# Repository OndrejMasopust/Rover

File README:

DO NOT USE ANYTHING FROM THIS REPOSITORY AS THIS PROJECT IS NOT FINISHED YET

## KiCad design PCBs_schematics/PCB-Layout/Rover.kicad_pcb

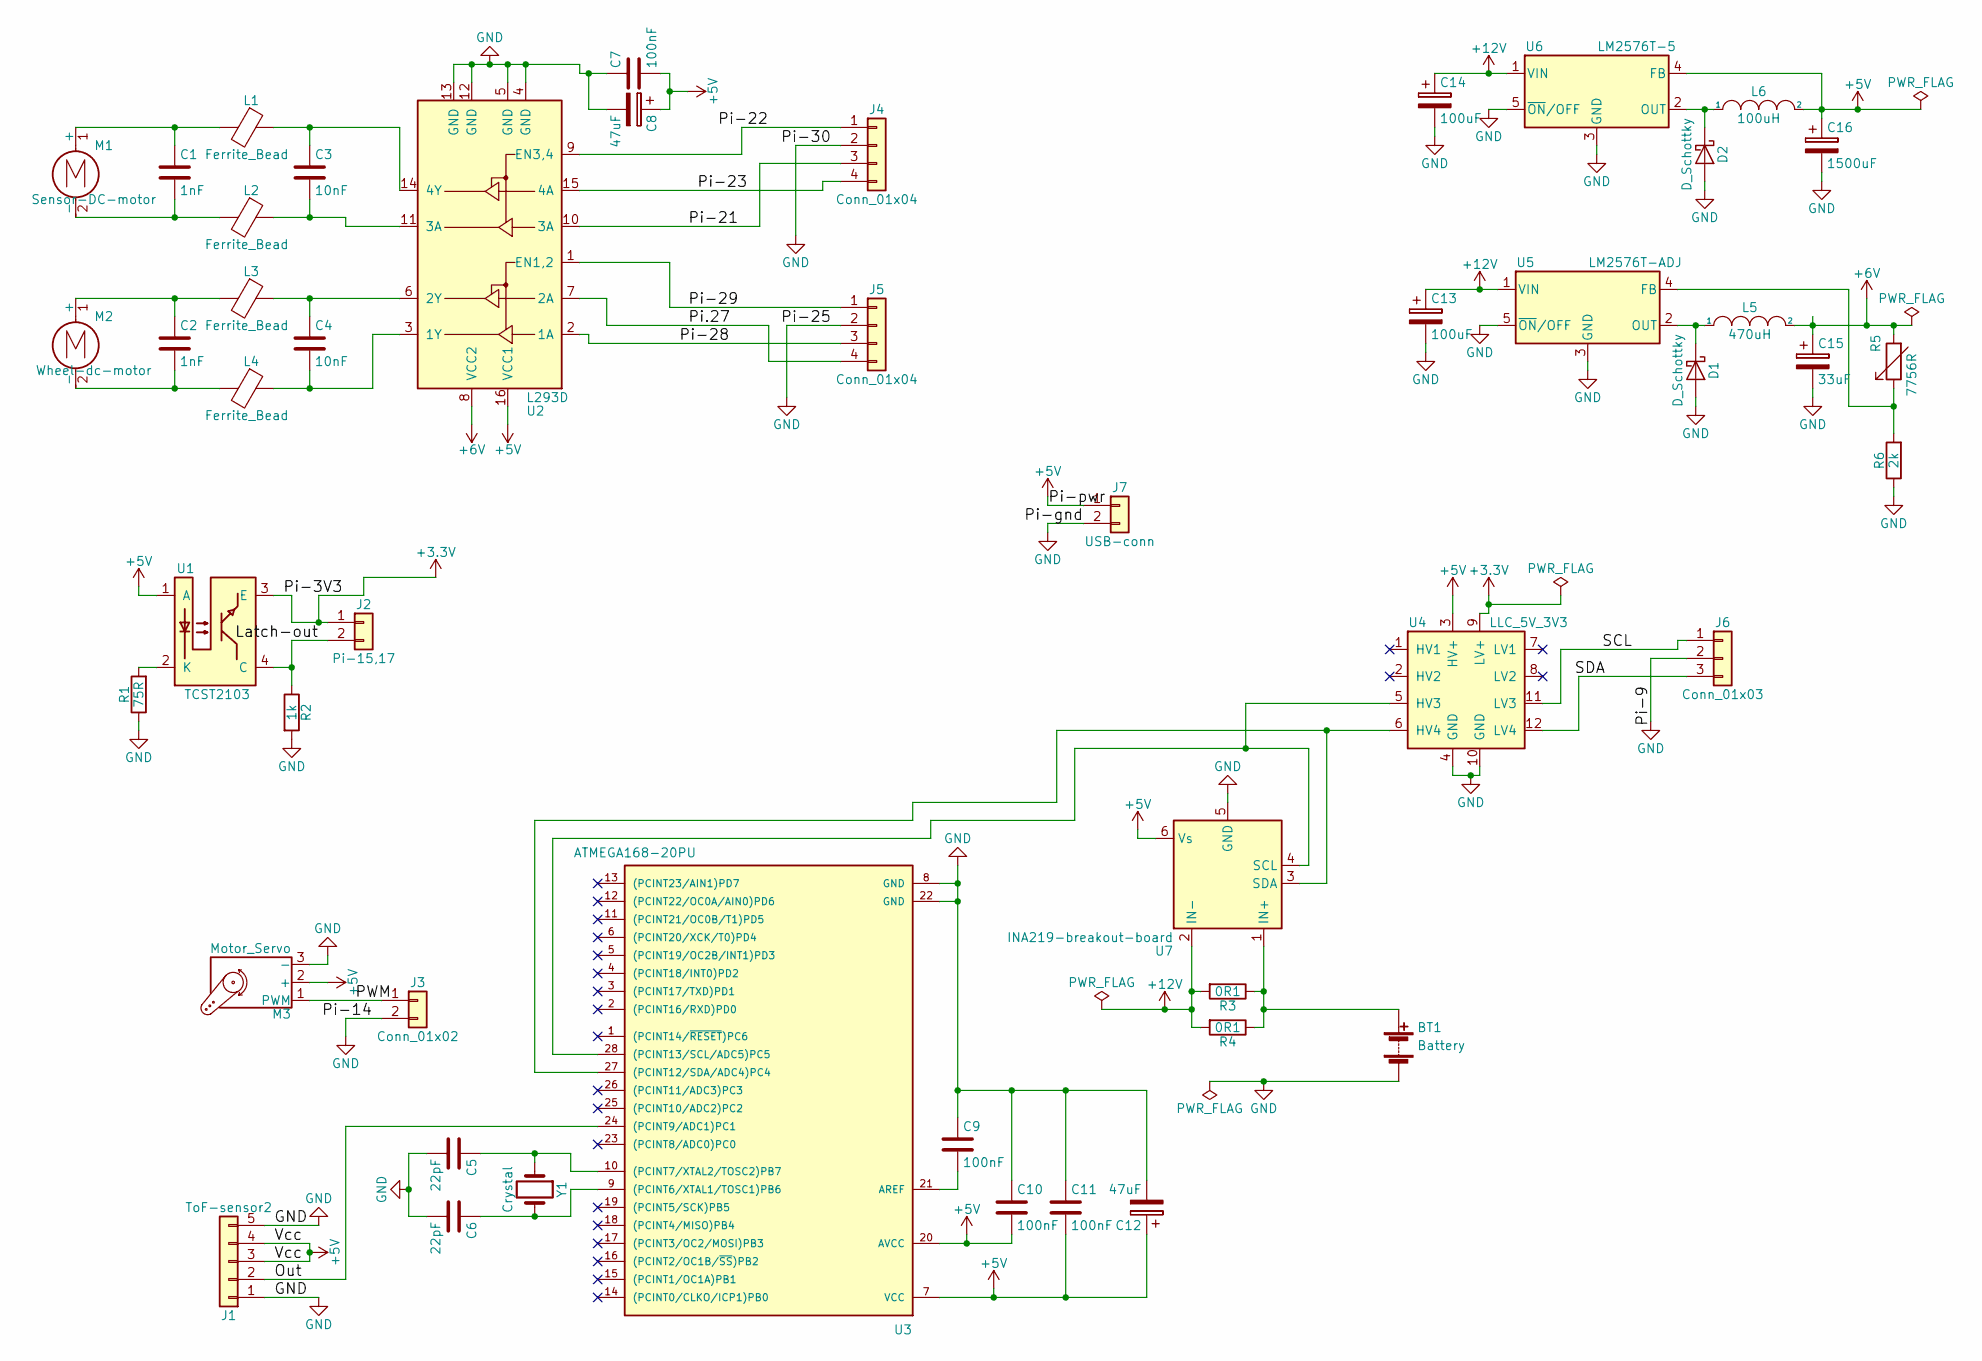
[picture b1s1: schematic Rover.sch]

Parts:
BT1: Battery; WireConnection_0.80mmDrill
C1, C2: 1nF; C_Rect_L7_W2_P5
C3, C4: 10nF; C_Rect_L4_W2.5_P2.5
C5, C6: 22pF; C_Rect_L7_W2_P5
C7, C9, C10, C11: 100nF; C_Rect_L4_W2.5_P2.5
C8, C12: 47uF; C_Rect_L4_W2.5_P2.5
C13: 100uF; C_Rect_L7_W2_P5
C14: 100uF; C_Rect_L4_W2.5_P2.5
C15: 33uF; C_Rect_L4_W2.5_P2.5
C16: 1500uF; C_Rect_L7_W2.5_P5
D1, D2: D_Schottky; Diode_DO-201AD_Horizontal_RM15
J1: ToF-sensor2; Pin_Header_Straight_1x05
J2: Pi-15,17; Pin_Header_Straight_1x02
J3: Conn_01x02; Pin_Header_Straight_1x02
J4, J5: Conn_01x04; Pin_Header_Straight_1x04
J6: Conn_01x03; Pin_Header_Straight_1x03
J7: USB-conn; Pin_Header_Straight_1x02
L1, L2, L3, L4: Ferrite_Bead; WireConnection_2.50mmDrill
L5: 470uH; Resistor_Horizontal_RM7mm
L6: 100uH; Resistor_Horizontal_RM10mm
M1: Sensor-DC-motor; Pin_Header_Straight_1x02
M2: Wheel-dc-motor; Pin_Header_Straight_1x02
M3: Motor_Servo; Pin_Header_Straight_1x03
R1: 75R; Resistor_Horizontal_RM10mm
R2: 1k; Resistor_Horizontal_RM10mm
R3, R4: 0R1; Resistor_Horizontal_RM20mm
R5: 7756R; Potentiometer_Trimmer-Suntan-TSR-3386C
R6: 2k; Resistor_Horizontal_RM10mm
U1: TCST2103; Pin_Header_Straight_1x04
U2: L293D; DIP-16_W7.62mm
U3: ATMEGA168-20PU; DIP-28_W7.62mm
U4: LLC_5V_3V3; LLC-header
U5: LM2576T-ADJ; Pentawatt_Neutral_Straight_Vertical_TO220-5-T05A
U6: LM2576T-5; Pentawatt_Neutral_Straight_Vertical_TO220-5-T05A
U7: INA219-breakout-board; Pin_Header_Straight_1x06
Y1: Crystal; Crystal_HC49-U_Vertical

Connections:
+3V3: J2.1, U1.3 (E), U4.9 (LV+)
+5V: C7.2, C8.1, C10.2, C11.2, C12.1, C16.1, J1.3, J1.4, J7.1, L6.2, M3.2 (+), U1.1 (A), U2.16 (VCC1), U3.7 (VCC), U3.20 (AVCC), U4.3 (HV+), U6.4 (FB), U7.6 (Vs)
+6V: C15.1, L5.2, R5.2, U2.8 (VCC2)
+12V: C13.1, C14.1, R3.2, R4.2, U5.1 (VIN), U6.1 (VIN), U7.2 (IN-)
/Latch-out: J2.2, R2.1, U1.4 (C)
/Out: J1.2, U3.24 ((PCINT9/ADC1)PC1)
/PWM: J3.1, M3.1 (PWM)
/Pi-21: J4.3, U2.10 (3A)
/Pi-22: J4.1, U2.9 (EN3,4)
/Pi-23: J4.4, U2.15 (4A)
/Pi-28: J5.3, U2.2 (1A)
/Pi-29: J5.1, U2.1 (EN1,2)
/Pi.27: J5.4, U2.7 (2A)
/SCL: J6.1, U4.11 (LV3)
/SDA: J6.3, U4.12 (LV4)
GND: BT1.2 (-), C5.2, C6.2, C7.1, C8.2, C9.1, C10.1, C11.1, C12.2, C13.2, C14.2, C15.2, C16.2, D1.2 (A), D2.2 (A), J1.1, J1.5, J3.2, J4.2, J5.2, J6.2, J7.2, M3.3 (-), R1.1, R2.2, R6.1, U2.4 (GND), U2.5 (GND), U2.12 (GND), U2.13 (GND), U3.8 (GND), U3.22 (GND), U4.4 (GND), U4.10 (GND), U5.3 (GND), U5.5 (~ON~/OFF), U6.3 (GND), U6.5 (~ON~/OFF), U7.5 (GND)
unnamed: BT1.1 (+), R3.1, R4.1, U7.1 (IN+)
unnamed: C1.1, L1.2, M1.1 (+)
unnamed: C1.2, L2.2, M1.2 (-)
unnamed: C2.1, L3.2, M2.1 (+)
unnamed: C2.2, L4.2, M2.2 (-)
unnamed: C3.1, L1.1, U2.14 (4Y)
unnamed: C3.2, L2.1, U2.11 (3A)
unnamed: C4.1, L3.1, U2.6 (2Y)
unnamed: C4.2, L4.1, U2.3 (1Y)
unnamed: C5.1, U3.10 ((PCINT7/XTAL2/TOSC2)PB7), Y1.1
unnamed: C6.1, U3.9 ((PCINT6/XTAL1/TOSC1)PB6), Y1.2
unnamed: C9.2, U3.21 (AREF)
unnamed: D1.1 (K), L5.1, U5.2 (OUT)
unnamed: D2.1 (K), L6.1, U6.2 (OUT)
unnamed: R1.2, U1.2 (K)
unnamed: R5.1, R6.2, U5.4 (FB)
unnamed: U3.27 ((PCINT12/SDA/ADC4)PC4), U4.6 (HV4), U7.3 (SDA)
unnamed: U3.28 ((PCINT13/SCL/ADC5)PC5), U4.5 (HV3), U7.4 (SCL)

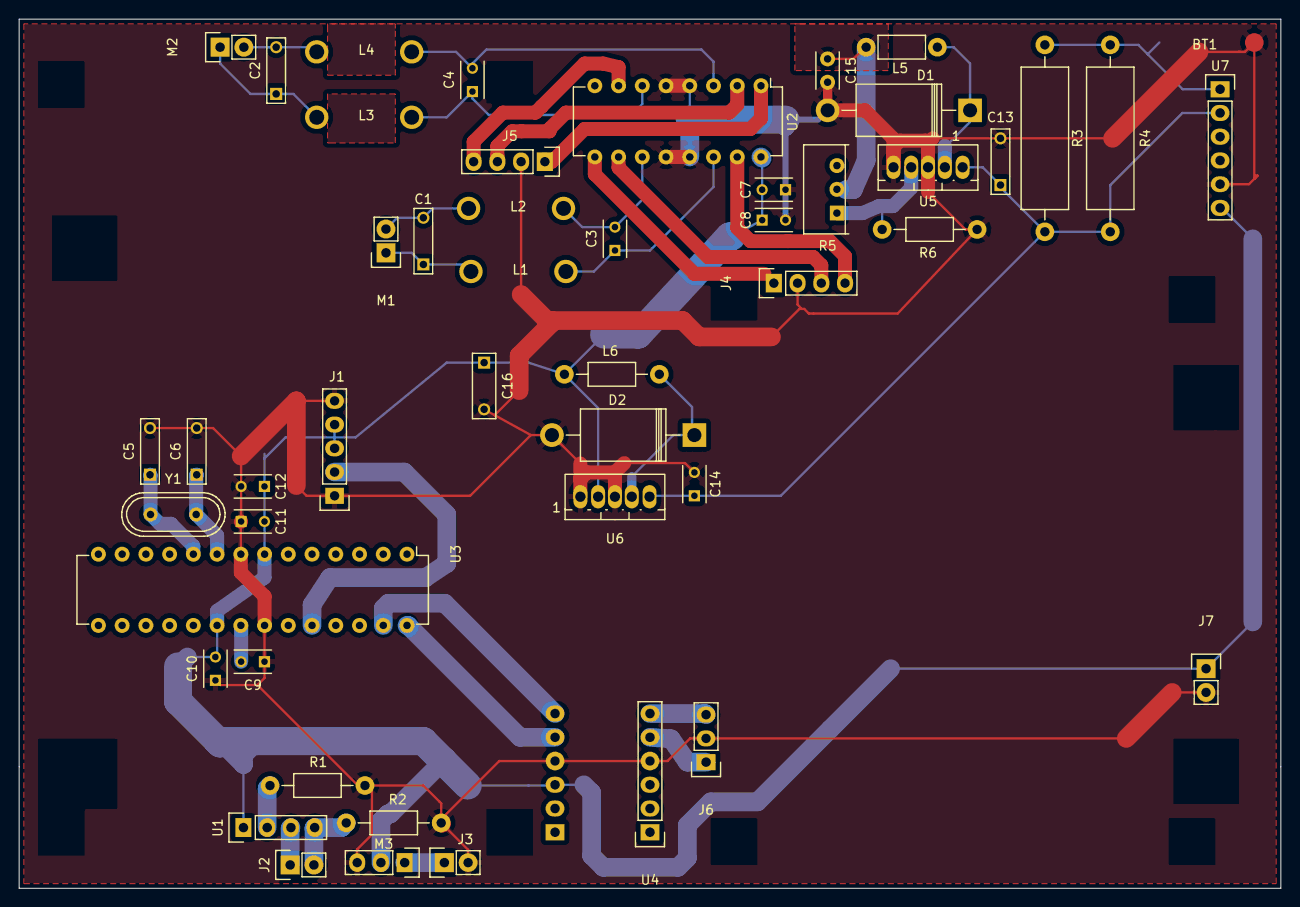
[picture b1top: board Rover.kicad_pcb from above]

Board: 2 copper layers, 135.0 x 93.0 mm, 49 parts (0 on the bottom side), 34 nets.

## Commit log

2017-08-16 Added .gitignore
2017-08-16 fixed bug where I couldn't access Pane from Java code
2017-08-17 compiled files excluded
2017-08-17 organized and added preloader
2017-08-17 preloader works while trying to connect to the Rover
2017-08-17 threads are working properly
2017-08-17 connection thread extends Task<Void>
2017-08-17 minor modifications
2017-08-18 minor changes
2017-08-20 error messages are written to the preloader
2017-08-23 IP selection window works somehow
2017-08-23 preloader in testing conditions, some work done to the rest
2017-08-23 preloader works good with the testing class
2017-08-23 preloader works good with the standard classes
2017-08-24 code cleaning and organizing
2017-08-25 comments added
2017-08-25 some work done
2017-08-26 some more work done on the main layout
2017-08-26 send messages appear on the right in the console
2017-08-28 info works somehow, need to finish it
2017-08-28 little progress
2017-08-29 info ready to edit and some work done on receiving from RPi
2017-08-29 receiving messages from the Rover should work
2017-08-30 adding messages to console works. auto.scroll of the console doesn't work
2017-08-31 console autoscroll in the main layout works
2017-09-01 more work done
2017-09-01 git repo moved one folder down
2017-09-01 some little cleaning
2017-09-01 added server socket testing class that doesn't work properly
2017-09-01 added heading to the console
2017-09-04 progress in the python files
2017-10-09 added event handlers for arrow keys that don't work properly
2017-10-09 now event handlers work unless focus is on the console input TextBox
2017-10-09 arrow key events now work properly but still not finished
2017-10-21 styled the whole app and changed arrow key events to switch-case
2017-10-21 excluded original images
2017-11-13 Lego added and some minor modifications in the software that I don't know what they are.
2017-11-13 progress on lego
2017-11-13 deleted compiled files and edited .gitignore to not track these files
2017-11-29 car design progress
2017-12-31 I2C test were successful
2018-01-03 AVR code is working for 2 sensors
2018-01-20 percentage added to the application and motor and servo drivers tested on RPi
2018-01-23 cleaned some minor errors in the last commit
2018-01-24 anchor commit before doing something crazy
2018-01-27 edited schematics, progress on the Rover software
2018-01-27 added README
2018-02-01 md edit
2018-02-02 commented all necessary in the Python code and renamed PCBs folder to PCBs_schematics
2018-02-02 progress on the python code, cleaned testing python modules into 'test' packages
2018-02-03 Java app now sends 'stop' when closing and waits for the Rover to ACK that
2018-02-03 deleted I2C class from the python code as it ws not used
2018-02-03 Java app can display errors in red, Python sometimes sends them and some more work done
2018-02-03 delted Errors to show in red because it's more difficult than I thought it would be
2018-02-05 Java app receives 'dt' correctly
2018-02-23 added 6V buck-converter version to the schematic
2018-02-23 fixed writing 'bt' commands to the console
2018-02-23 error messages show again in red and every new message has its own box
2018-03-03 progress on the PCB
2018-03-06 more progress on the PCBs
2018-03-07 ferrite beads pads smallered
2018-03-07 edited pcb files for production
2018-03-15 first step of designing mounts of the PCB on the Rover
2018-03-16 some more work done on the Rover Lego design
2018-03-16 final Rover design
2018-03-23 added building instructions for the Rover
2018-03-29 added Credits.md
2018-03-29 edited Credits.md
2018-03-30 fixed defining unused pins on the AVR for lower power consumption
2018-03-30 renamed General-scheme folder
2018-03-30 added the ability to stop the sensor temporarily
2018-03-30 pigpiod server now starts from the Python script
2018-03-31 renamed folder and added value to the crytal
2018-04-02 servo works, main motor changes direction, but the enums for changing directions are not treated as booleans
2018-04-02 added credits for the send arrow icon in the main layout
2018-04-02 edited credits
2018-04-02 added credits to Blackberry for their colot pallete
2018-04-02 added link to the documentation in the README.md
2018-04-02 some testing
2018-04-02 edited comments
2018-04-02 pigpiod server is now stopped when the program is ending
2018-04-02 edited HoeTo.md
2018-04-02 edited Rover lego design
2018-04-02 just save before some experiments
2018-04-02 some code cleaning
2018-04-02 added info to the main layout as html
2018-04-02 save after generating the building instructions
2018-04-02 experiment
2018-04-02 edited HowTo.md
2018-04-02 edited .gitignore
2018-04-02 deleted I2C.rtf from the git repo
2018-04-02 added documentation for the C and edited HowTo
2018-04-04 fixed AVR I2C bug, now it responses to the i2cdetect
2018-04-10 translated HowTo to czech
2018-04-10 edited docs/
2018-04-10 python code works, but queues slow it down, commit before testing Pipe
2018-04-11 exchanged threading.Event instead of queue, between main thread and sensor thread
2018-04-13 commit before testing sending data without the select.select()
2018-04-13 sensing still does not work as expected
2018-04-13 data processing is not fast enough
2018-04-13 deleted pyc files and directories
2018-04-13 ignoring *pyc* files
2018-04-13 Python code shortened, processing data is fast enough
2018-04-13 Java code accepts new type of 'dt' messages, but hangs on quit when the sensor is running
2018-04-14 final changes to the Java program
2018-04-14 almost done
2018-04-14 minor edits to the Java app and finished build.xml
2018-04-14 deleted IPHostPrompt class, because it is not easy to write into a file inside a jar archive
2018-04-14 edited testing Main.py to its previous form
2018-04-14 deleted the BattertyPercentageManager, because it is not easy to write into a file inside a jar archive
2018-04-14 tank dimensions are more realistic
2018-04-14 changed colors to the dots and lines in the main layout center section
2018-04-14 deleted unnecessary project files from the AVR/ folder
2018-04-14 servo is centered
2018-04-14 edited Lego design - removed differential
2018-04-14 edited doc comments in Java so that they do not contain the {@code} blocks
2018-04-14 edited Python doc strings
2018-04-14 generated programmers documentation
2018-04-14 moved docs files one folder up
2018-04-14 edited docs
2018-04-14 added user manual
2018-04-14 renamed the jar file
2018-04-14 Python program does not print neither rotation time nor the number of sent data
2018-04-14 added picture of the main layout with description
2018-04-15 edited documentation
2018-04-15 Create LICENSE
2018-04-15 added licence to the source code files
2018-04-15 added necessary files from the build folder
2018-04-15 edited car-BOM.xlsx
2018-04-15 solved some FIXMEs and deleted the rest of them
2018-04-15 edited README.md
2018-04-15 edite docs/
2018-04-15 edited sources in the ProgDoc
